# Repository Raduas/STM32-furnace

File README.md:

# STM32 Induction Furnace

A personal project focused on designing and building a resonant H-bridge induction furnace controlled by an STM32 microcontroller.

This was my first larger electronics project and gave me hands-on experience with power electronics, control systems, PCB design, and embedded software development.

The furnace was not completed as a final product, but core functionality was successfully tested. Maximum achieved temperature reached the Curie point.

# Challenges
Learning the fundamentals of power electronics.
Understanding resonant circuits and H-bridge operation.
Designing reliable gate driver circuits.
Managing electrical noise and ground isolation.
Debugging hardware and software interactions.
Developing and tuning control algorithms.

# Lessons Learned

Through this project, I gained practical experience in:

Power electronics design.
Designing power supplies with multiple voltage levels.
STM32 development using STM32CubeIDE.
Implementing control algorithms for an H-bridge inverter.
Applying Ohm's Law and basic circuit analysis in real-world situations.
Reading and understanding component datasheets.
PCB design, including gate driver layout and ground isolation.
Using laboratory equipment such as oscilloscopes and multimeters.
System debugging and troubleshooting.

## PCB Design

## Schematic

## Assebled PCB

# Future Improvements

If I were to redesign the system today, I would:

Improve thermal management and cooling.
Reconsider the overall system architecture.
Spend more time on mathematical analysis before implementation.
Perform more simulations and design reviews early in development.
Add additional protection features and fault detection mechanisms.
Improve PCB layout to reduce noise and simplify debugging.

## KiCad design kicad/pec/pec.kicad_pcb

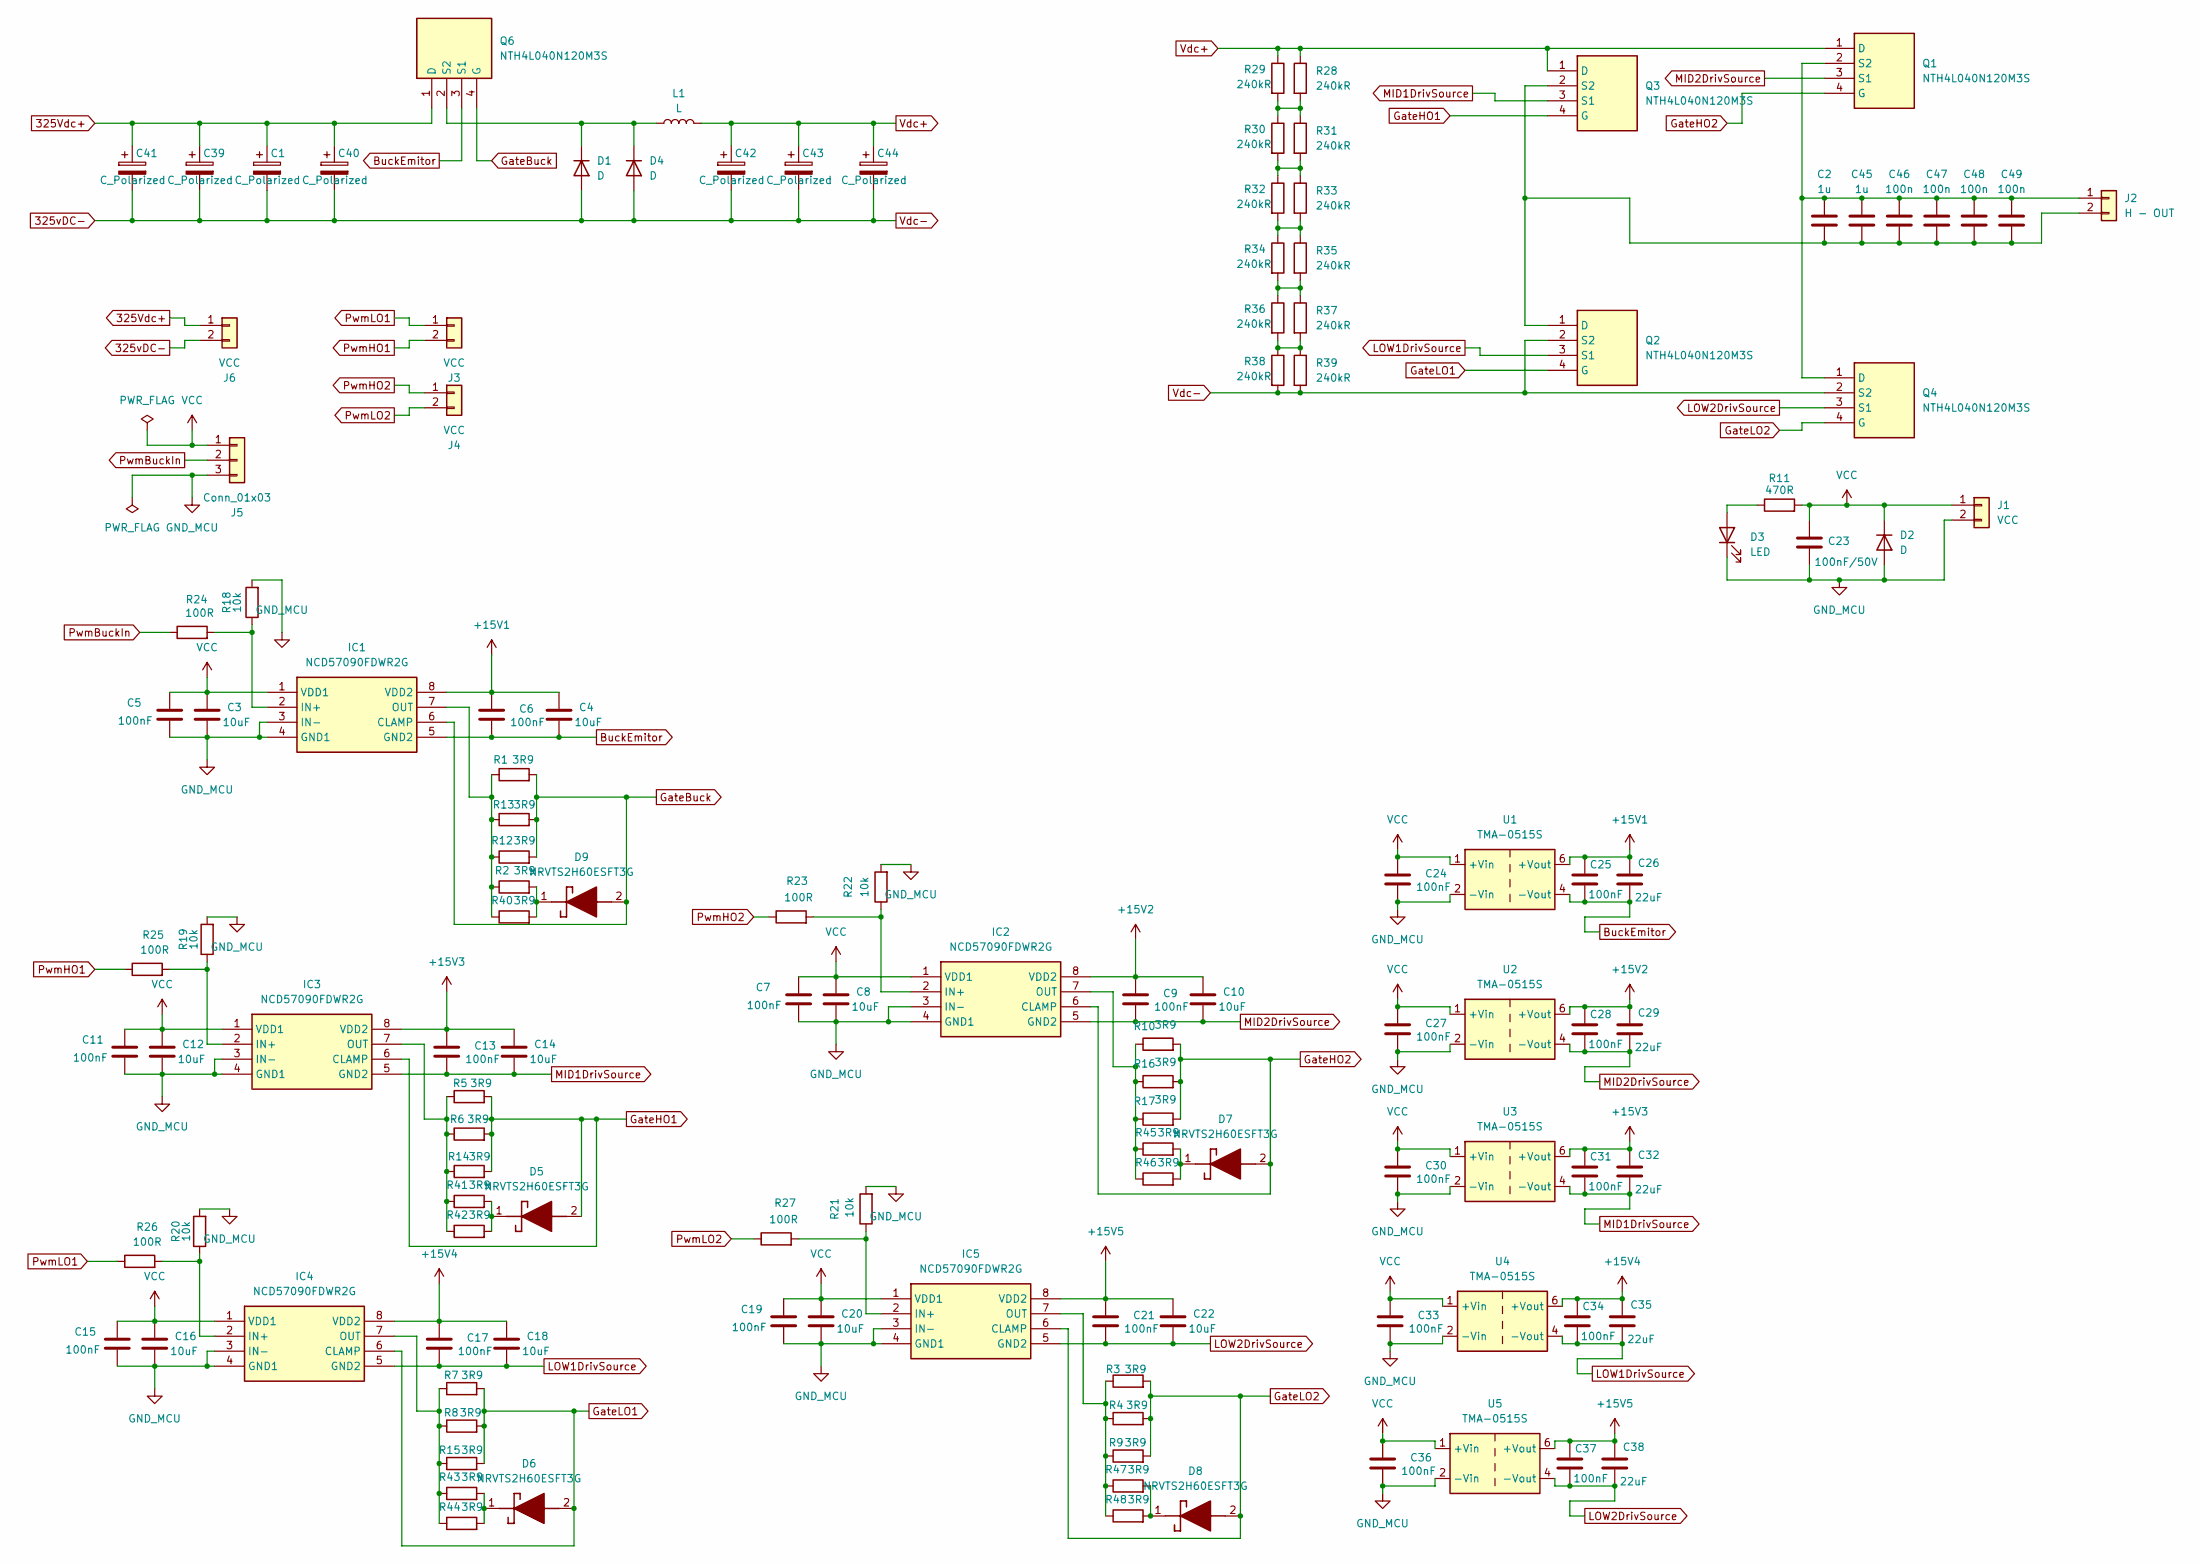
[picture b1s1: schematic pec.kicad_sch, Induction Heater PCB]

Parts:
C1, C39, C40, C41, C42, C43, C44: C_Polarized; CP_Radial_D22.0mm_P10.00mm_SnapIn
C2, C45: 1u; C_Rect_L29.0mm_W13.0mm_P27.50mm_MKT
C3, C4, C8, C10, C12, C14, C16, C18, C20, C22: 10uF; C_0805_2012Metric_Pad1.18x1.45mm_HandSolder
C5, C6, C7, C9, C11, C13, C15, C17, C19, C21, C24, C25, C27, C28, C30, C31, C33, C34, C36, C37: 100nF; C_0603_1608Metric_Pad1.08x0.95mm_HandSolder
C23: 100nF/50V; C_0603_1608Metric_Pad1.08x0.95mm_HandSolder
C26, C29, C32, C35, C38: 22uF; C_1210_3225Metric_Pad1.33x2.70mm_HandSolder
C46, C47, C48, C49: 100n; C_Rect_L19.0mm_W8.0mm_P15.00mm_MKS4
D1, D4: D; D_P600_R-6_P12.70mm_Horizontal
D2: D; D_SOD-123
D3: LED; LED_1206_3216Metric_Pad1.42x1.75mm_HandSolder
D5, D6, D7, D8, D9: NRVTS2H60ESFT3G; SODFL3616X98N; Manufacturer_Part_Number NRVTS2H60ESFT3G; Mouser Part Number 863-NRVTS2H60ESFT3G
IC1, IC2, IC3, IC4, IC5: NCD57090FDWR2G; SOIC127P1031X265-8N; Manufacturer_Part_Number NCD57090FDWR2G; Mouser Part Number 863-NCD57090FDWR2G
J1, J3, J4: VCC; TerminalBlock_MetzConnect_Type055_RT01502HDWU_1x02_P5.00mm_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
J2: H - OUT; PhoenixContact_GMSTBA_2,5_2-G-7,62_1x02_P7.62mm_Horizontal
J5: Conn_01x03; TerminalBlock_MetzConnect_Type055_RT01503HDWU_1x03_P5.00mm_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
J6: VCC; PhoenixContact_GMSTBA_2,5_2-G-7,62_1x02_P7.62mm_Horizontal
L1: L; L_Toroid_Vertical_L48.8mm_W25.4mm_P20.80mm_Vishay_TJ8
Q1, Q2, Q3, Q4, Q6: NTH4L040N120M3S; Manufacturer_Part_Number NTH4L040N120M3S; Mouser Part Number 863-NTH4L040N120M3S
R1, R2, R3, R4, R5, R6, R7, R8, R9, R10, R12, R13, R14, R15, R16, R17, R40, R41, R42, R43, R44, R45, R46, R47, R48: 3R9; R_1206_3216Metric_Pad1.30x1.75mm_HandSolder
R11: 470R; R_0805_2012Metric_Pad1.20x1.40mm_HandSolder
R18, R19, R20, R21, R22: 10k; R_0805_2012Metric_Pad1.20x1.40mm_HandSolder
R23, R24, R25, R26, R27: 100R; R_0805_2012Metric_Pad1.20x1.40mm_HandSolder
R28, R29, R30, R31, R32, R33, R34, R35, R36, R37, R38, R39: 240kR; R_1206_3216Metric_Pad1.30x1.75mm_HandSolder
U1, U2, U3, U4, U5: TMA-0515S; Converter_DCDC_TRACO_TMA-05xxS_12xxS_Single_THT

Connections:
325Vdc+: C1.1, C39.1, C40.1, C41.1, J6.1, Q6.1 (D)
325vDC-: C1.2, C39.2, C40.2, C41.2, C42.2, C43.2, C44.2, D1.2 (A), D4.2 (A), J6.2, Q2.2 (S2), Q4.2 (S2), R38.2, R39.2
+15V1: C4.2, C6.2, C25.2, C26.2, IC1.8 (VDD2), U1.6 (+Vout)
+15V2: C9.2, C10.2, C28.2, C29.2, IC2.8 (VDD2), U2.6 (+Vout)
+15V3: C13.2, C14.2, C31.2, C32.2, IC3.8 (VDD2), U3.6 (+Vout)
+15V4: C17.2, C18.2, C34.2, C35.2, IC4.8 (VDD2), U4.6 (+Vout)
+15V5: C21.2, C22.2, C37.2, C38.2, IC5.8 (VDD2), U5.6 (+Vout)
BuckEmitor: C4.1, C6.1, C25.1, C26.1, IC1.5 (GND2), Q6.3 (S1), U1.4 (-Vout)
GND_MCU: C3.1, C5.1, C7.1, C8.1, C11.1, C12.1, C15.1, C16.1, C19.1, C20.1, C23.1, C24.1, C27.1, C30.1, C33.1, C36.1, D2.2 (A), D3.1 (K), IC1.3 (IN-), IC1.4 (GND1), IC2.3 (IN-), IC2.4 (GND1), IC3.3 (IN-), IC3.4 (GND1), IC4.3 (IN-), IC4.4 (GND1), IC5.3 (IN-), IC5.4 (GND1), J1.2, J5.3, R18.2, R19.2, R20.2, R21.2, R22.2, U1.2 (-Vin), U2.2 (-Vin), U3.2 (-Vin), U4.2 (-Vin), U5.2 (-Vin)
GateBuck: D9.2 (A), IC1.6 (CLAMP), Q6.4 (G), R1.2, R12.2, R13.2
GateHO1: D5.2 (A), IC3.6 (CLAMP), Q3.4 (G), R5.2, R6.2, R14.2
GateHO2: D7.2 (A), IC2.6 (CLAMP), Q1.4 (G), R10.2, R16.2, R17.2
GateLO1: D6.2 (A), IC4.6 (CLAMP), Q2.4 (G), R7.2, R8.2, R15.2
GateLO2: D8.2 (A), IC5.6 (CLAMP), Q4.4 (G), R3.2, R4.2, R9.2
LOW1DrivSource: C17.1, C18.1, C34.1, C35.1, IC4.5 (GND2), Q2.3 (S1), U4.4 (-Vout)
LOW2DrivSource: C21.1, C22.1, C37.1, C38.1, IC5.5 (GND2), Q4.3 (S1), U5.4 (-Vout)
MID1DrivSource: C13.1, C14.1, C31.1, C32.1, IC3.5 (GND2), Q3.3 (S1), U3.4 (-Vout)
MID2DrivSource: C9.1, C10.1, C28.1, C29.1, IC2.5 (GND2), Q1.3 (S1), U2.4 (-Vout)
unnamed: D1.1 (K), D4.1 (K), L1.1, Q6.2 (S2)
unnamed: D3.2 (A), R11.1
unnamed: D5.1 (K), R41.2, R42.2
unnamed: D6.1 (K), R43.2, R44.2
unnamed: D7.1 (K), R45.2, R46.2
unnamed: D8.1 (K), R47.2, R48.2
unnamed: D9.1 (K), R2.2, R40.2
unnamed: IC1.2 (IN+), R18.1, R24.2
unnamed: IC1.7 (OUT), R1.1, R2.1, R12.1, R13.1, R40.1
unnamed: IC2.2 (IN+), R22.1, R23.2
unnamed: IC2.7 (OUT), R10.1, R16.1, R17.1, R45.1, R46.1
unnamed: IC3.2 (IN+), R19.1, R25.2
unnamed: IC3.7 (OUT), R5.1, R6.1, R14.1, R41.1, R42.1
unnamed: IC4.2 (IN+), R20.1, R26.2
unnamed: IC4.7 (OUT), R7.1, R8.1, R15.1, R43.1, R44.1
unnamed: IC5.2 (IN+), R21.1, R27.2
unnamed: IC5.7 (OUT), R3.1, R4.1, R9.1, R47.1, R48.1
unnamed: C2.2, C45.2, C46.2, C47.2, C48.2, C49.2, J2.1, Q1.2 (S2), Q4.1 (D)
unnamed: C2.1, C45.1, C46.1, C47.1, C48.1, C49.1, J2.2, Q2.1 (D), Q3.2 (S2)
unnamed: R28.2, R29.2, R30.1, R31.1
unnamed: R30.2, R31.2, R32.1, R33.1
unnamed: R32.2, R33.2, R34.1, R35.1
unnamed: R34.2, R35.2, R36.1, R37.1
unnamed: R36.2, R37.2, R38.1, R39.1
PwmBuckIn: J5.2, R24.1
PwmHO1: J3.2, R25.1
PwmHO2: J4.1, R23.1
PwmLO1: J3.1, R26.1
PwmLO2: J4.2, R27.1
VCC: C3.2, C5.2, C7.2, C8.2, C11.2, C12.2, C15.2, C16.2, C19.2, C20.2, C23.2, C24.2, C27.2, C30.2, C33.2, C36.2, D2.1 (K), IC1.1 (VDD1), IC2.1 (VDD1), IC3.1 (VDD1), IC4.1 (VDD1), IC5.1 (VDD1), J1.1, J5.1, R11.2, U1.1 (+Vin), U2.1 (+Vin), U3.1 (+Vin), U4.1 (+Vin), U5.1 (+Vin)
Vdc+: C42.1, C43.1, C44.1, L1.2, Q1.1 (D), Q3.1 (D), R28.1, R29.1

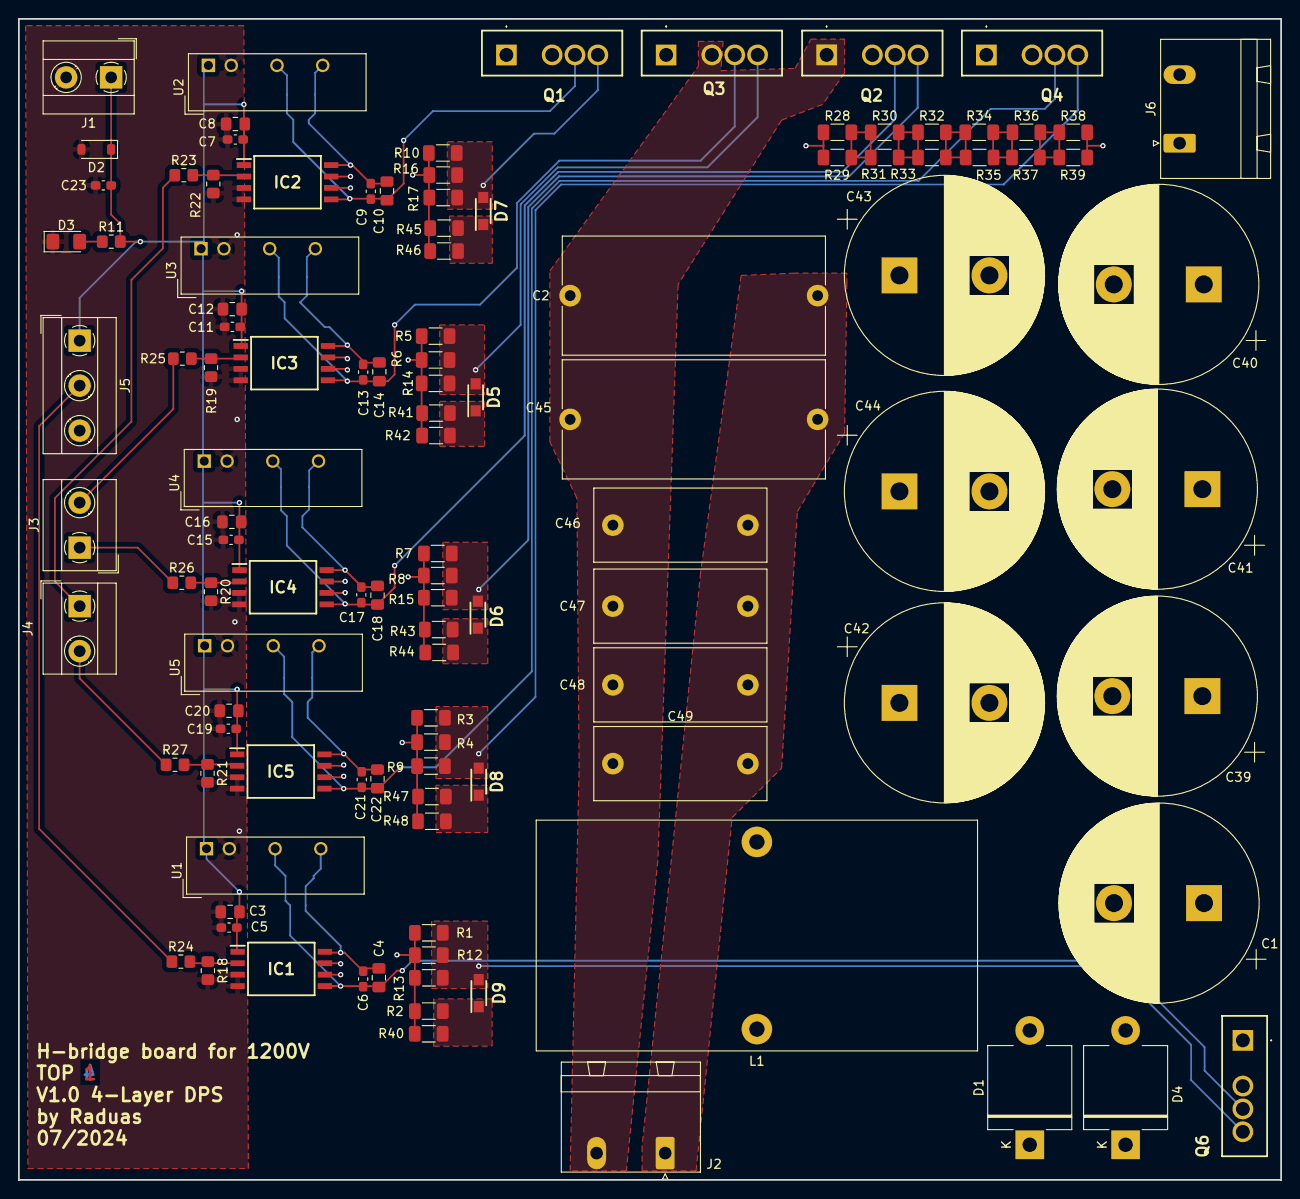
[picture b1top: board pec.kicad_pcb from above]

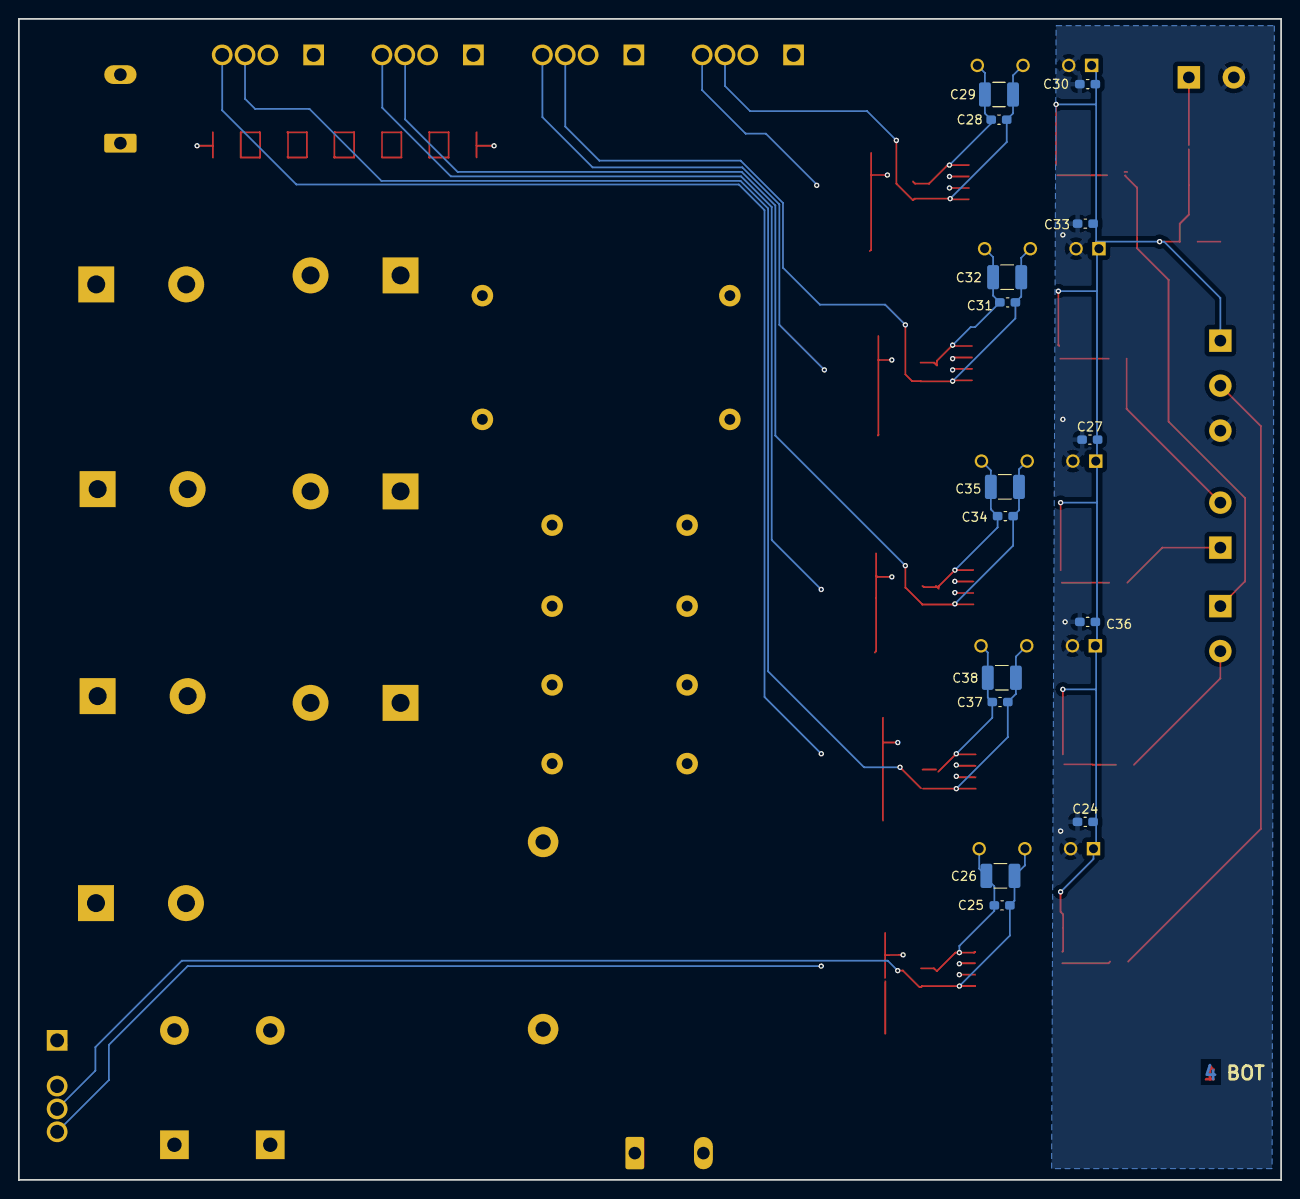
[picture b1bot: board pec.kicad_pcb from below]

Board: 4 copper layers, 140.2 x 129.0 mm, 128 parts (15 on the bottom side), 49 nets.

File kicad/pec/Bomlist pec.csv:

'Reference'; 'Value'; 'Datasheet'; 'Footprint'; 'Qty'; 'DNP'
'C1,C39,C40,C41,C42,C43,C44'; 'C_Polarized'; '~'; 'Capacitor_THT:CP_Radial_D22.0mm_P10.00mm_SnapIn'; '7'; ''
'C2,C45'; '1u'; '~'; 'Capacitor_THT:C_Rect_L29.0mm_W13.0mm_P27.50mm_MKT'; '2'; ''
'C3,C4,C8,C10,C12,C14,C16,C18,C20,C22'; '10uF'; '~'; 'Capacitor_SMD:C_0805_2012Metric_Pad1.18x1.45mm_HandSolder'; '10'; ''
'C5,C6,C7,C9,C11,C13,C15,C17,C19,C21,C24,C25,C27,C28,C30,C31,C33,C34,C36,C37'; '100nF'; '~'; 'Capacitor_SMD:C_0603_1608Metric_Pad1.08x0.95mm_HandSolder'; '20'; ''
'C23'; '100nF/50V'; '~'; 'Capacitor_SMD:C_0603_1608Metric_Pad1.08x0.95mm_HandSolder'; '1'; ''
'C26,C29,C32,C35,C38'; '22uF'; '~'; 'Capacitor_SMD:C_1210_3225Metric_Pad1.33x2.70mm_HandSolder'; '5'; ''
'C46,C47,C48,C49'; '100n'; '~'; 'Capacitor_THT:C_Rect_L19.0mm_W8.0mm_P15.00mm_MKS4'; '4'; ''
'D1,D2,D4'; 'D'; '~'; '-- mixed values --'; '3'; ''
'D3'; 'LED'; '~'; 'LED_SMD:LED_1206_3216Metric_Pad1.42x1.75mm_HandSolder'; '1'; ''
'D5,D6,D7,D8,D9'; 'NRVTS2H60ESFT3G'; 'https://www.onsemi.com/pub/Collateral/NRVTS2H60ESF-D.PDF'; 'SODFL3616X98N'; '5'; ''
'IC1,IC2,IC3,IC4,IC5'; 'NCD57090FDWR2G'; 'https://www.onsemi.com/pub/Collateral/NCD57090A-D.PDF'; 'SOIC127P1031X265-8N'; '5'; ''
'J1,J3,J4,J6'; 'VCC'; '~'; '-- mixed values --'; '4'; ''
'J2'; 'H - OUT'; '~'; 'Connector_Phoenix_GMSTB:PhoenixContact_GMSTBA_2,5_2-G-7,62_1x02_P7.62mm_Horizontal'; '1'; ''
'J5'; 'Conn_01x03'; '~'; 'TerminalBlock_MetzConnect:TerminalBlock_MetzConnect_Type055_RT01503HDWU_1x03_P5.00mm_Horizontal'; '1'; ''
'L1'; 'L'; '~'; 'Inductor_THT:L_Toroid_Vertical_L48.8mm_W25.4mm_P20.80mm_Vishay_TJ8'; '1'; ''
'Q1,Q2,Q3,Q4,Q6'; 'NTH4L040N120M3S'; 'https://www.onsemi.com/pub/Collateral/NTH4L040N120M3S-D.PDF'; 'NTH4L040N120M3S'; '5'; ''
'R1,R2,R3,R4,R5,R6,R7,R8,R9,R10,R12,R13,R14,R15,R16,R17,R40,R41,R42,R43,R44,R45,R46,R47,R48'; '3R9'; '~'; 'Resistor_SMD:R_1206_3216Metric_Pad1.30x1.75mm_HandSolder'; '25'; ''
'R11'; '470R'; '~'; 'Resistor_SMD:R_0805_2012Metric_Pad1.20x1.40mm_HandSolder'; '1'; ''
'R18,R19,R20,R21,R22'; '10k'; '~'; 'Resistor_SMD:R_0805_2012Metric_Pad1.20x1.40mm_HandSolder'; '5'; ''
'R23,R24,R25,R26,R27'; '100R'; '~'; 'Resistor_SMD:R_0805_2012Metric_Pad1.20x1.40mm_HandSolder'; '5'; ''
'R28,R29,R30,R31,R32,R33,R34,R35,R36,R37,R38,R39'; '240kR'; '~'; 'Resistor_SMD:R_1206_3216Metric_Pad1.30x1.75mm_HandSolder'; '12'; ''
'U1,U2,U3,U4,U5'; 'TMA-0515S'; 'https://www.tracopower.com/products/tma.pdf'; 'Converter_DCDC:Converter_DCDC_TRACO_TMA-05xxS_12xxS_Single_THT'; '5'; ''

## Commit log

2026-06-25 full project to git
2026-06-25 Revise README with detailed project overview
    Expanded project description and added sections on challenges, lessons learned, PCB design, and future improvements.
2026-06-25 photos from projects
2026-06-25 Update PCB image format from JPG to PNG
